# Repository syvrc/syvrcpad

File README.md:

## syvrcpad
> I made this because I wanted to try something new and to feel useful to myself 💀 and ofcourse to make something which I would use in my daily life to probably save some extra clicks and miliseconds.

> `syvrcpad` is a 4x3 (4 by 3) macropad with a `rotary encoder E11` and has `0.91 OLED Display`. The macropad uses `XIAO RP2040` as its micro controller.

## build
> well um yeah 💀, this is not soldered btw, i jus added switches and the xiao to it cuz it looks cool sybau and ooh also i made use of an old charger cable of my phone

> i originally did not have a soldering iron/kit but then i did `#solder` and got one, turns out the whole soldering iron of the kit is messed up which took me `5 diodes`, `3 pcbs` and `the whole solder wire of the kit` to figure out. and i crashed out bad, anw now idts i will be able to make ts so now im working on a keeb called [syvrcboard v0](https://github.com/syvrc/syvrcboard-v0) with an integrated macropad boii
## Schematic

## PCB
PCB Front           |  PCB Back
:-------------------------:|:-------------------------:|
    |  
> I had the most fun making schematic and PCB, tho I had to do both of these quite a lot of time 💀 I have routed the PCB like minimum 8 times if not more. Being a complete beginner and having no clue what you are doing is really fun, I am pretty sure I annoyed hell lotta people in the `#highway` and `#hackpad` channel lmao and special thanks to `@Ayo`, `@Domain` and `@Cyao` (on slack) and many other people who helped me through this journey and making this project possible.

## Layers

> My initial plan was to make Top, Middle and Bottom layers but I just ended up with Top and Bottom layers because it was taking way too much time than expected and planned. Im pretty happy and proud of what I have made btw 🗣

> Thickness of Plate: 1.5mm  
> Thickness of Bottom: 10mm  

## Render of the PCB with all the components

## Side View

> Made the USB C port more accessible and ofcoure more visually appealing

## Closing and Thank You!
> Being able to do something like this was REALLY fun, loved and enjoyed every second of it  
> Learned some basics of Kicad  
> Learned Shaper3d (moderately)  
> Learned what a Keyboard matrix is and how it works  
> Learned few keyboard mounting methods  
> Maybe it was the friends we made throgh the journey  

## BOM
> 11x Blank DSA Keycaps (Black if possible)  
> 11x Cherry MX Switches  
> 12x 1N4148 diodes  
> 1x XIAO RP2040  
> 4x M3x16mm Screw Bolt  
> 4x M3 Heatset  
> 1x Conn_01x04 (for the 0.91 OLED screen: check schematic for more clarity)  
> 1x EC11 Rotary Encoder  
> 1x Rotary Encoder Knob  
> 1x PCB  
> 1x Case (I would like the TOP to be printed in Red and BOTTOM in Black, if not available: Message me @syvr on Slack)

---
> ~~hit the like button~~ star the repo if you like my work!! 🚶‍♂️

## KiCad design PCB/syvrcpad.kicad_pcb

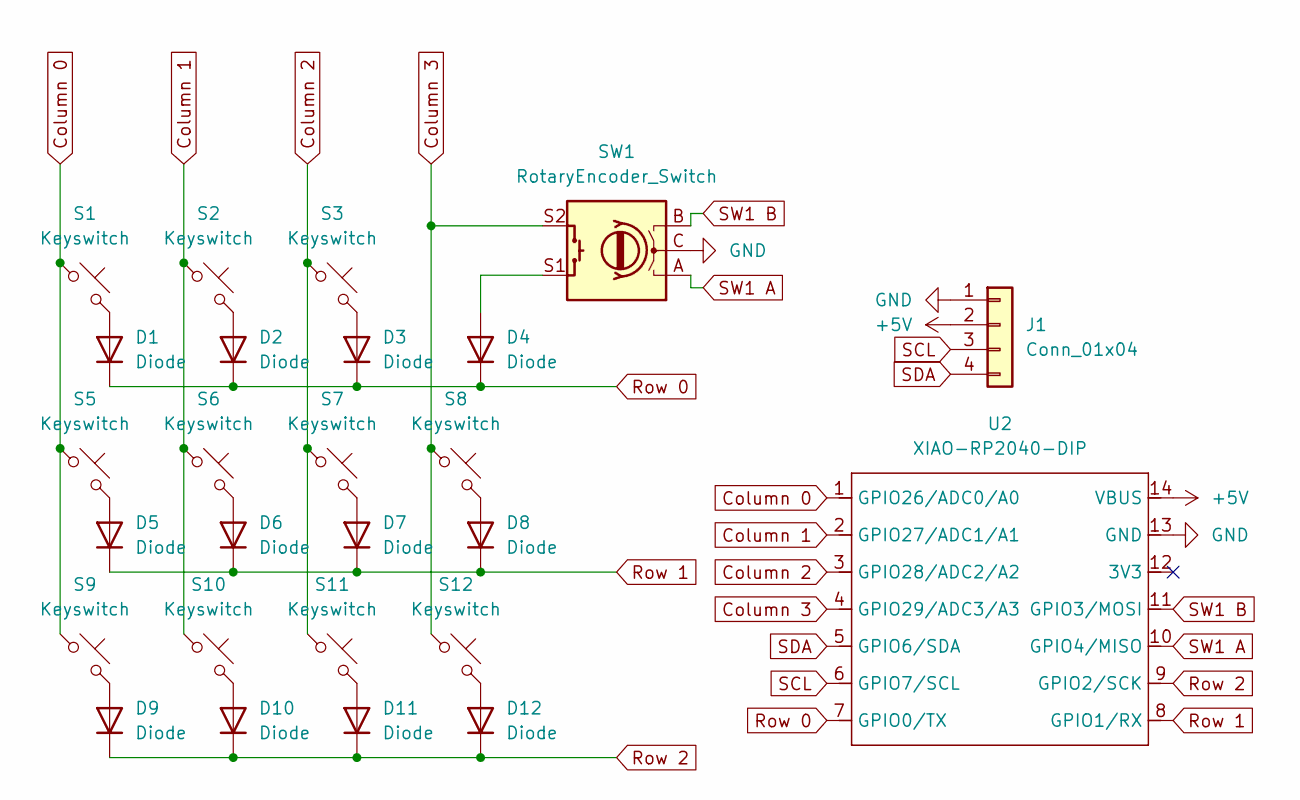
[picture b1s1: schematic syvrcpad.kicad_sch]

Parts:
D1, D2, D3, D4, D5, D6, D7, D8, D9, D10, D11, D12: Diode; Diode_DO-35
J1: Conn_01x04; SSD1306-0.91-OLED-4pin-128x32
S1, S2, S3, S5, S6, S7, S8, S9, S10, S11, S12: Keyswitch; SW_Cherry_MX_1.00u_PCB
SW1: RotaryEncoder_Switch; RotaryEncoder_Alps_EC11E-Switch_Vertical_H20mm_CircularMoun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
U2: XIAO-RP2040-DIP

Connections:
+5V: J1.2, U2.14 (VBUS)
Column 0: S1.1, S5.1, S9.1, U2.1 (GPIO26/ADC0/A0)
Column 1: S2.1, S6.1, S10.1, U2.2 (GPIO27/ADC1/A1)
Column 2: S3.1, S7.1, S11.1, U2.3 (GPIO28/ADC2/A2)
Column 3: S8.1, S12.1, SW1.S2, U2.4 (GPIO29/ADC3/A3)
GND: J1.1, SW1.C, U2.13 (GND)
unnamed: D1.2 (A), S1.2
unnamed: D2.2 (A), S2.2
unnamed: D3.2 (A), S3.2
unnamed: D4.2 (A), SW1.S1
unnamed: D5.2 (A), S5.2
unnamed: D6.2 (A), S6.2
unnamed: D7.2 (A), S7.2
unnamed: D8.2 (A), S8.2
unnamed: D9.2 (A), S9.2
unnamed: D10.2 (A), S10.2
unnamed: D11.2 (A), S11.2
unnamed: D12.2 (A), S12.2
Row 0: D1.1 (K), D2.1 (K), D3.1 (K), D4.1 (K), U2.7 (GPIO0/TX)
Row 1: D5.1 (K), D6.1 (K), D7.1 (K), D8.1 (K), U2.8 (GPIO1/RX)
Row 2: D9.1 (K), D10.1 (K), D11.1 (K), D12.1 (K), U2.9 (GPIO2/SCK)
SCL: J1.3, U2.6 (GPIO7/SCL)
SDA: J1.4, U2.5 (GPIO6/SDA)
SW1 A: SW1.A, U2.10 (GPIO4/MISO)
SW1 B: SW1.B, U2.11 (GPIO3/MOSI)

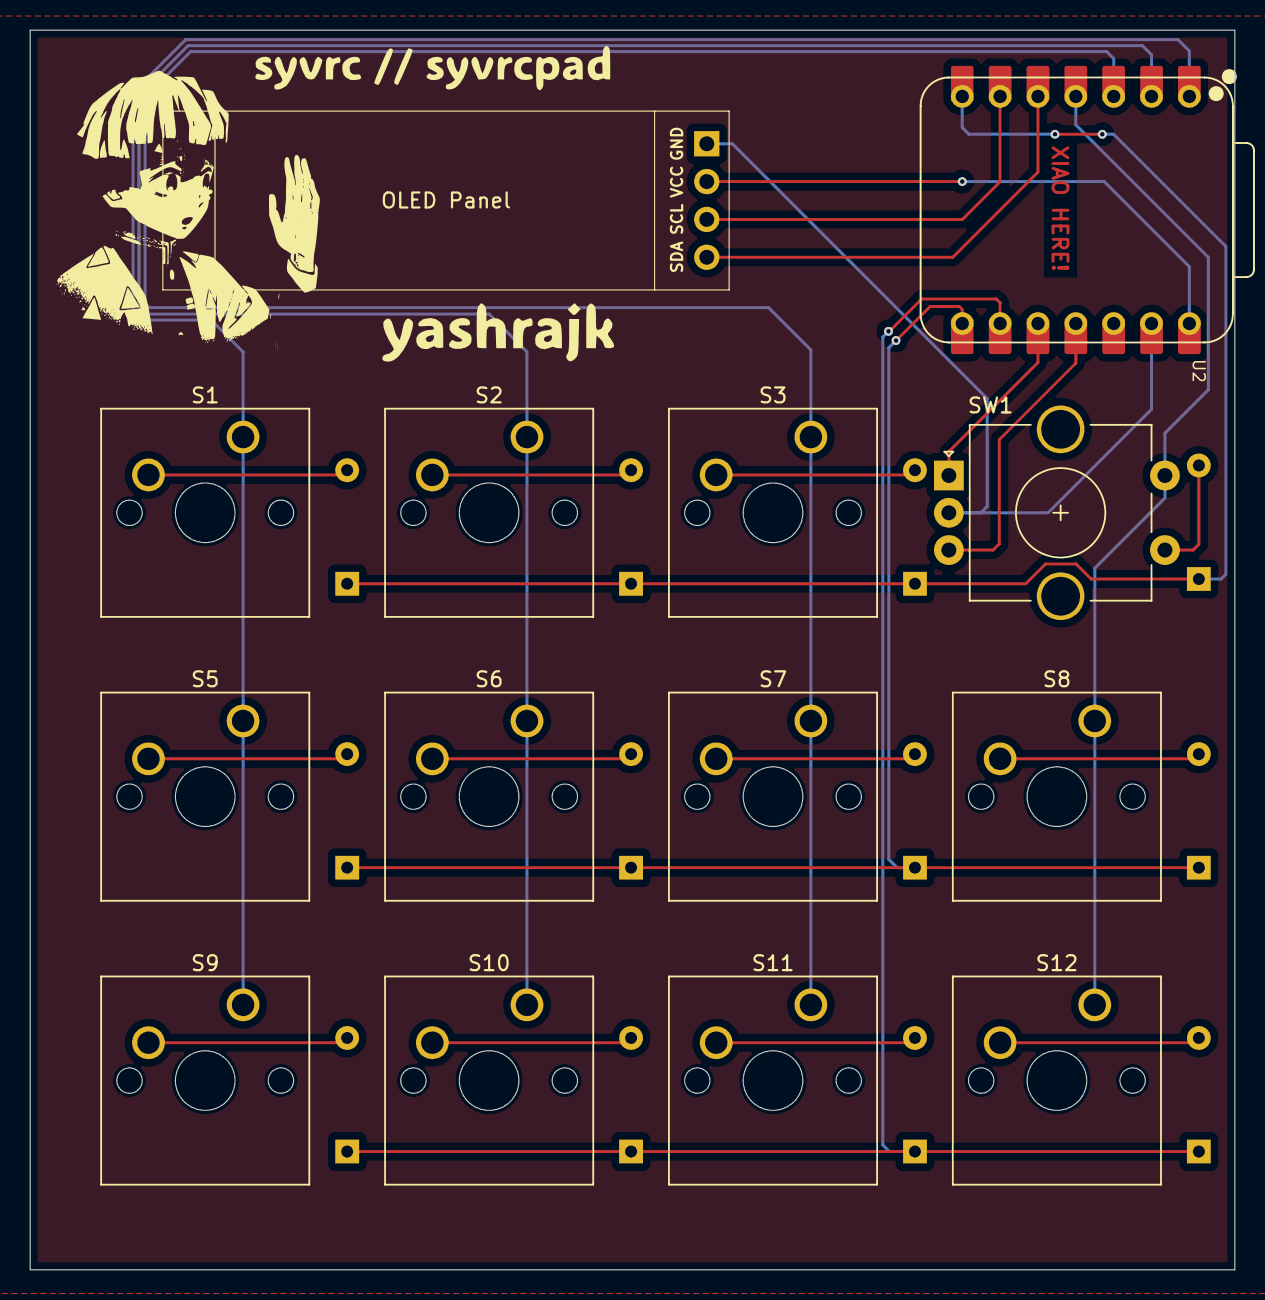
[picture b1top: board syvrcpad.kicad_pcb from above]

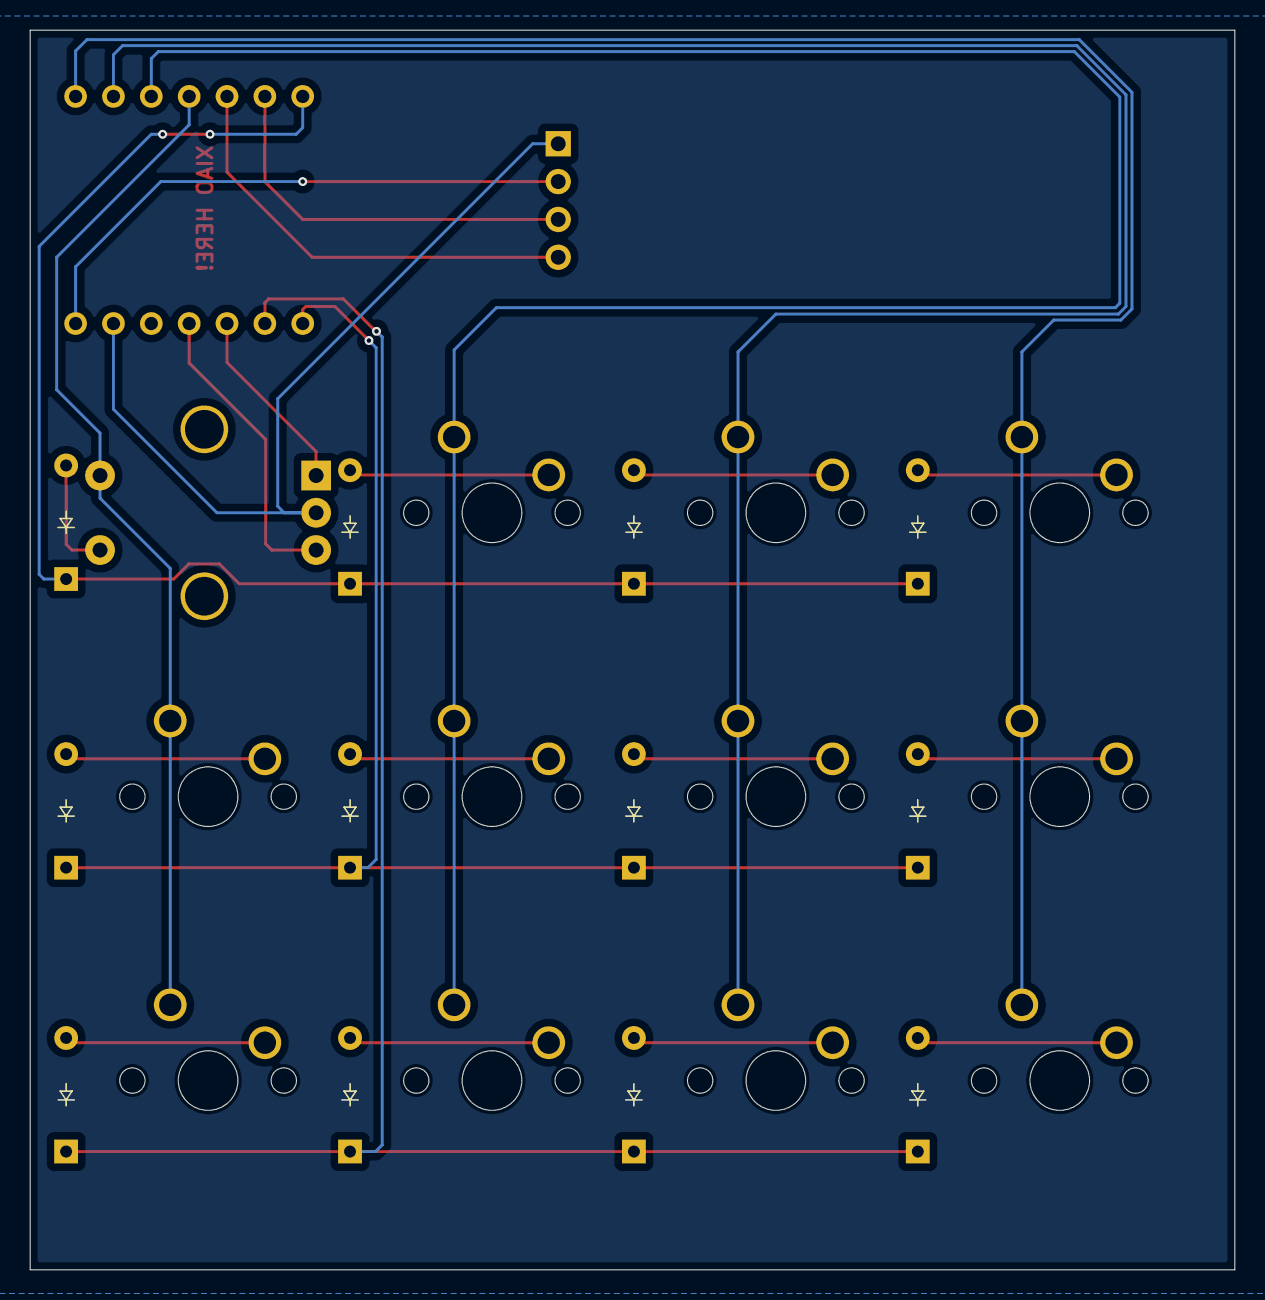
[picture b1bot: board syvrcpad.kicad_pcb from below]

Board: 2 copper layers, 80.8 x 83.2 mm, 26 parts (12 on the bottom side), 25 nets.

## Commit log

2025-05-31 .step
2025-05-31 syvrcpad
2025-05-31 imgs
2025-05-31 images
2025-05-31 README.md
2025-05-31 spacing
2025-05-31 content
2025-05-31 fixation
2025-05-31 appeal
2025-05-31 insa
2025-05-31 lmao
2025-05-31 json
2025-05-31 donee less goo
2025-05-31 Closing section
2025-05-31 did sum research
2025-05-31 grammar
2025-06-11 license
2025-07-05 present
2025-07-05 present: first draft
2025-07-05 present: second draft
2025-07-05 build: third draft
2025-07-05 build: fourth draft
2025-07-05 build: fix
